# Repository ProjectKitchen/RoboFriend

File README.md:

# Robofriend

Robofriend - a semi-autonomous, remotely controllable robot companion.

Robofriend - initially created by Tom Heike 2002 - was exhibited at several Roboexotica events, serving drinks at the Vienniese Cocktail Robot Festival.
In 2014, two Robofriends were donated by Tom to us, and were further developed by Dr. Wummi and Karima Khlousy-Neirukh and other students at UAS Technikum Wien, in order to make Robofriend a playful companion robot which can be evaluated together with kids with special needs in selected schools in Vienna.
For this purpose, several game applications were developed which involve robot movements and expressions.

## Features
* live video transmission (low latency, < 300ms)
* remote control via webbrowser or game apps
* proximity sensors for collision avoidance & activity detection
* facial expressions, sound/voice playback, illuminated ears
* RFID reader - utilized for game interaction
* unique design (with CRT-head) by Tom Heike

## System Architecture / Components

The Robofriend uses a Teensy++ 2.0 microcontroller to handle motor control, led lights, servos, proximity sensors and battery status...
The Teensy is connected to the RaspberryPi via USB (/dev/ttyACM0). The RaspberryPi communicates with the Teensy via a simple protocol (ASCII-commands).
The RaspberryPi handles most of the robot's functions such as: RFID reader, CRT monitor, video camera, LED ears, speech output, ...

## User Interface and Control Options

The RaspberryPi starts a webserver which provides a webpage with live video feed and control interface.
It can be reached via http://<ip-adress-of-raspberry>:8765

The webpage uses an API to control the robots functions - this API is described in the theses of Karima Khlousy Neirukh (folder /documentation).
Furthermore, dedicated games have been developed by Karima which utilize the RFID-reader so that kids can use physical objects to interact with the robo and play litte games (identify animal sounds, emotions etc.)
These game applications are also written in python and are usually launched on a seperated tablet computer. The tablet connect to the python main script via a UDP connection (port 9000) and uses the same commands as the web GUI. It is planned to use a REST API for both (webpage and tablet GUI).

## Requirements

**Mjpg-Streamer:**
*  [MJPEG-Streamer Install & Setup](https://github.com/cncjs/cncjs/wiki/Setup-Guide:-Raspberry-Pi-%7C-MJPEG-Streamer-Install-&-Setup-&-FFMpeg-Recording)

**OpenCV 3:**
* To install OpenCV 3 on a Raspberry Pi 3 follow the following tutorial (except the virtual environment part):
[OpenCV 3 on Raspberry Pi 3](https://www.pyimagesearch.com/2017/09/04/raspbian-stretch-install-opencv-3-python-on-your-raspberry-pi/)

**Roboter Operating System (ROS):**
* To install ROS on your computing unit (Laptop or Rasberry Pi 3) follow [these instructions](https://github.com/ProjectKitchen/RoboFriend/tree/ros-node-devel/src/Pi/scripts)

**LIDAR - 360 laser distance sensor lds-01:**
* Manufacturer's [site](http://www.robotis.us/360-laser-distance-sensor-lds-01-lidar/)
* Set permission for the LDS-01 sensor after connecting it to the USB interface:
   * sudo chmod a+rw /dev/ttyUSBx

## Additional Information

* We recommand you to clone the repository into a folder named *Git* placed in your home directory (~/Git/)
* After pulling the repository, execute following commands (see the ROS install instructions):
   * cd ~/Git/RoboFriend/src/Pi/catkin_ws/ && rm -r build/ && rm -r devel/ && catkin_make clean && catkin_make && catkin_make
* To start face detection and object detection on external laptop enter *./start_computervision.sh "IP_ADDRESS_OF_RASPBERRY_PI"*

## Setup

Setup scripts are provided in folder /src/Pi/scripts

## Startup

Startup scripts are provided in folder /src/Pi/

## Future Plans

As next steps, several high-levels skills for Robofriend are planned:
* indoor localisation using ROS navigation stack (in order to find charging station)
* speech interaction (mic-array, beamforming, DOA, hotword detection)
* image analysis of live camera feed (face detection, facial landmark classification)

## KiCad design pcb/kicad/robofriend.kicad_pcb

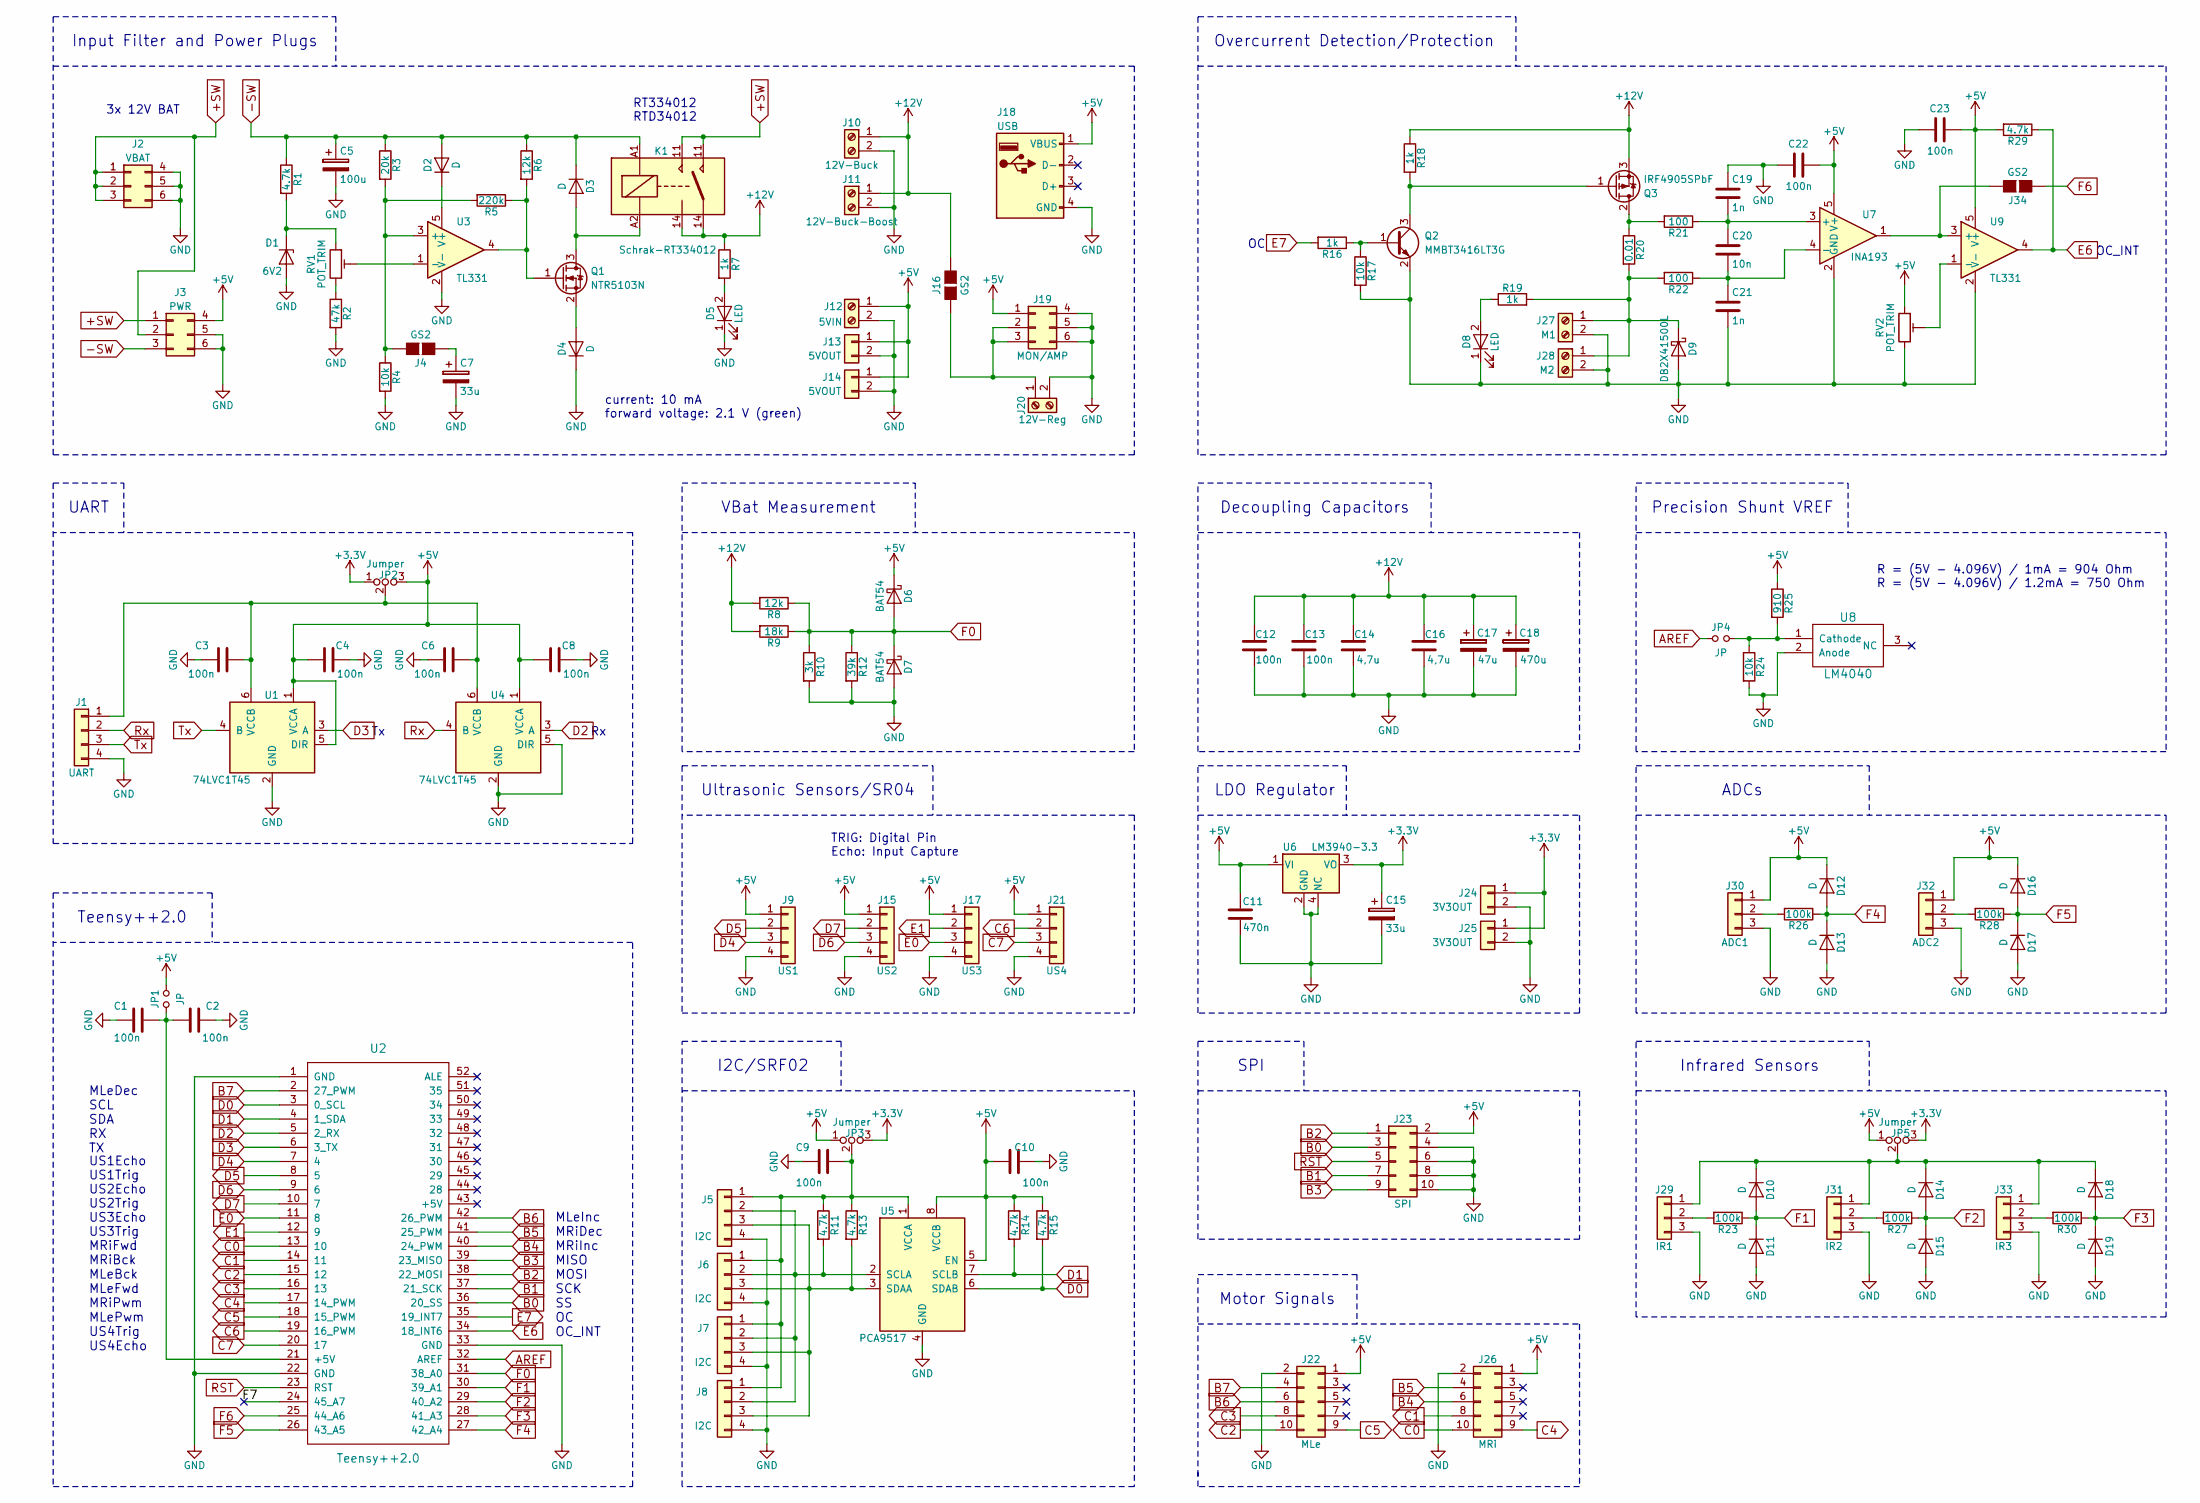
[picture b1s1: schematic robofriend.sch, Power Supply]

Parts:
C1, C2, C3, C4, C6, C8, C9, C10: 100n; C_0603
C5: 100u; CP_Elec_6.3x5.7; Part No EEE1CA101WAP
C7: 33u; CP_Elec_5x5.7; Part No EEE1CA330WR
C11: 470n; C_0805
C12, C13, C22, C23: 100n; C_0805
C14, C16: 4,7u; C_0805
C15: 33u; CP_Elec_4x5.7; Part No EEE0JA330WR
C17: 47u; CP_Elec_6.3x5.8; Part No EEEFK1C470P
C18: 470u; CP_Elec_8x10.5; Part No EEEFK1C471P
C19, C21: 1n; C_0805
C20: 10n; C_0805
D1: 6V2; D_SOD-123
D2, D4: D; D_SOD-323
D3: D; D_SOD-123
D5, D8: LED; LED_0805
D6, D7: BAT54; D_SOD-323; Part No BAT54WS-7-F
D9: DB2X41500L; D_SOD-123; Part No DB2X41500L
D10, D11, D12, D13, D14, D15, D16, D17, D18, D19: D; D_SOD-523
J1: UART; Pin_Header_Straight_1x04_Pitch2.54mm
J2: VBAT; Molex_MiniFit-JR-5556-06A_2x03x4.20mm_Straight
J3: PWR; Molex_MiniFit-JR-5556-06A_2x03x4.20mm_Straight
J4, J16, J34: GS2
J5, J6, J7, J8: I2C; Pin_Header_Straight_1x04_Pitch2.54mm
J9: US1; Pin_Header_Straight_1x04_Pitch2.54mm
J10: 12V-Buck; Molex_MiniFit-JR-5556-02B_2x01x4.20mm_Straight
J11: 12V-Buck-Boost; Molex_MiniFit-JR-5556-02B_2x01x4.20mm_Straight
J12: 5VIN; Molex_MiniFit-JR-5556-02B_2x01x4.20mm_Straight
J13, J14: 5VOUT; Pin_Header_Straight_2x01_Pitch2.54mm
J15: US2; Pin_Header_Straight_1x04_Pitch2.54mm
J17: US3; Pin_Header_Straight_1x04_Pitch2.54mm
J18: USB; WURTH_61400416021; Part No 48258-0001
J19: MON/AMP; Molex_MiniFit-JR-5556-06A_2x03x4.20mm_Straight
J20: 12V-Reg; Molex_MiniFit-JR-5556-02B_2x01x4.20mm_Straight
J21: US4; Pin_Header_Straight_1x04_Pitch2.54mm
J22: MLe; Pin_Header_Straight_2x05_Pitch2.54mm
J23: SPI; Pin_Header_Straight_2x05_Pitch2.54mm
J24, J25: 3V3OUT; Pin_Header_Straight_2x01_Pitch2.54mm
J26: MRi; Pin_Header_Straight_2x05_Pitch2.54mm
J27: M1; Molex_MiniFit-JR-5556-02B_2x01x4.20mm_Straight
J28: M2; Molex_MiniFit-JR-5556-02B_2x01x4.20mm_Straight
J29: IR1; Pin_Header_Straight_1x03_Pitch2.54mm
J30: ADC1; Pin_Header_Straight_1x03_Pitch2.54mm
J31: IR2; Pin_Header_Straight_1x03_Pitch2.54mm
J32: ADC2; Pin_Header_Straight_1x03_Pitch2.54mm
J33: IR3; Pin_Header_Straight_1x03_Pitch2.54mm
JP1, JP4: JP; Pin_Header_Straight_1x02_Pitch2.54mm
JP2, JP3, JP5: Jumper; Pin_Header_Straight_1x03_Pitch2.54mm
K1: Schrak-RT334012; SPST_Schrack-RT33_RM5mm
Q1: NTR5103N; SOT-23
Q2: MMBT3416LT3G; SOT-23
Q3: IRF4905SPbF; TO-263-2
R1, R29: 4.7k; R_0805
R2: 47k; R_0805
R3: 20k; R_0805
R4, R17: 10k; R_0805
R5: 220k; R_0805
R6, R8: 12k; R_0805
R7, R16, R18, R19: 1k; R_0805
R9: 18k; R_0805
R10: 3k; R_0805
R11, R13, R14, R15: 4.7k; R_0603
R12: 39k; R_0805
R20: 0.01; R_2512; Part No WSL2512R0100FEK
R21, R22: 100; R_0805
R23, R26, R27, R28, R30: 100k; R_0603
R24: 10k; R_0603
R25: 910; R_0603
RV1, RV2: POT_TRIM; Potentiometer_Trimmer_Bourns_3296W; Part No 3296W-1-104LF
U1, U4: 74LVC1T45; SOT-363_SC-70-6
U2: Teensy++2.0; Teensy2.0++
U3, U9: TL331; SOT-23-5
U5: PCA9517; SOIC-8_3.9x4.9mm_Pitch1.27mm
U6: LM3940-3.3; SOT-223
U7: INA193; SOT-23-5
U8: LM4040; SOT-23

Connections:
+3V3: C15.1, J24.1, J25.1, JP2.1, JP3.3, JP5.3, U6.3 (VO)
+5V: C4.1, C8.1, C10.1, C11.2, C22.2, C23.2, D6.1 (K), D12.1 (K), D16.1 (K), J3.4, J9.1, J12.1, J13.1, J14.1, J15.1, J17.1, J18.1 (VBUS), J19.1, J21.1, J22.1, J23.2, J26.1, J30.1, J32.1, JP1.2, JP2.3, JP3.1, JP5.1, R14.1, R15.1, R25.1, R29.2, RV2.1, U1.1 (VCCA), U1.5 (DIR), U4.1 (VCCA), U5.5 (EN), U5.8 (VCCB), U6.1 (VI), U7.5 (V+), U9.5 (V+)
+12V: C12.2, C13.2, C14.2, C16.2, C17.1, C18.1, J10.1, J11.1, J16.2 (G2), K1.14, Q3.3 (S), R7.1, R8.2, R9.2, R18.1
+SW: J2.1, J2.2, J2.3, J3.1, J3.2, K1.11
-SW: C5.1, D2.2 (A), D3.1 (K), J3.3, K1.A1, R1.1, R3.1, R6.1
AREF: JP4.1, U2.32 (AREF)
B0: J23.3, U2.36 (20_SS)
B1: J23.7, U2.37 (21_SCK)
B2: J23.1, U2.38 (22_MOSI)
B3: J23.9, U2.39 (23_MISO)
B4: J26.6, U2.40 (24_PWM)
B5: J26.4, U2.41 (25_PWM)
B6: J22.6, U2.42 (26_PWM)
B7: J22.4, U2.2 (27_PWM)
C0: J26.10, U2.13 (10)
C1: J26.8, U2.14 (11)
C2: J22.10, U2.15 (12)
C3: J22.8, U2.16 (13)
C4: J26.9, U2.17 (14_PWM)
C5: J22.9, U2.18 (15_PWM)
C6: J21.2, U2.19 (16_PWM)
C7: J21.3, U2.20 (17)
D0: R15.2, U2.3 (0_SCL), U5.6 (SDAB)
D1: R14.2, U2.4 (1_SDA), U5.7 (SCLB)
D2: U2.5 (2_RX), U4.3 (A)
D3: U1.3 (A), U2.6 (3_TX)
D4: J9.3, U2.7 (4)
D5: J9.2, U2.8 (5)
D6: J15.3, U2.9 (6)
D7: J15.2, U2.10 (7)
E0: J17.3, U2.11 (8)
E1: J17.2, U2.12 (9)
E6: R29.1, U2.34 (18_INT6), U9.4
E7: R16.2, U2.35 (19_INT7)
F0: D6.2 (A), D7.1 (K), R8.1, R9.1, R10.1, R12.1, U2.31 (38_A0)
F1: D10.2 (A), D11.1 (K), R23.1, U2.30 (39_A1)
F2: D14.2 (A), D15.1 (K), R27.1, U2.29 (40_A2)
F3: D18.2 (A), D19.1 (K), R30.1, U2.28 (41_A3)
F4: D12.2 (A), D13.1 (K), R26.1, U2.27 (42_A4)
F5: D16.2 (A), D17.1 (K), R28.1, U2.26 (43_A5)
F6: J34.1 (G1), U2.25 (44_A6)
GND: C1.2, C2.1, C3.2, C4.2, C5.2, C6.2, C7.2, C8.2, C9.2, C10.2, C11.1, C12.1, C13.1, C14.1, C15.2, C16.1, C17.2, C18.2, C19.1, C21.2, C22.1, C23.1, D1.2 (A), D4.1 (K), D5.1 (K), D7.2 (A), D8.1 (K), D9.2 (A), D11.2 (A), D13.2 (A), D15.2 (A), D17.2 (A), D19.2 (A), J1.4, J2.4, J2.5, J2.6, J3.5, J3.6, J5.4, J6.4, J7.4, J8.4, J9.4, J10.2, J11.2, J12.2, J13.2, J14.2, J15.4, J17.4, J18.4 (GND), J19.4, J19.5, J19.6, J20.2, J21.4, J22.2, J23.4, J23.6, J23.8, J23.10, J24.2, J25.2, J26.2, J27.2, J28.2, J29.3, J30.3, J31.3, J32.3, J33.3, Q2.2 (E), R2.2, R4.2, R10.2, R12.2, R17.2, R24.2, RV2.3, U1.2 (GND), U2.1 (GND), U2.22 (GND), U2.33 (GND), U3.2 (V-), U4.2 (GND), U4.5 (DIR), U5.4 (GND), U6.2 (GND), U6.4 (NC), U7.2 (GND), U8.2 (Anode), U9.2 (V-)
unnamed: C1.1, C2.2, JP1.1, U2.21 (+5V)
unnamed: C3.1, C6.1, J1.1, JP2.2, U1.6 (VCCB), U4.6 (VCCB)
unnamed: C7.1, J4.1 (G1)
unnamed: C9.1, J5.1, J6.1, J7.1, J8.1, JP3.2, R11.1, R13.1, U5.1 (VCCA)
unnamed: C19.2, C20.1, R21.1, U7.3 (+)
unnamed: C20.2, C21.1, R22.1, U7.4 (-)
unnamed: D1.1 (K), R1.2, RV1.1
unnamed: D2.1 (K), U3.5 (V+)
unnamed: D3.2 (A), K1.A2, Q1.3 (D)
unnamed: D4.2 (A), Q1.2 (S)
unnamed: D5.2 (A), R7.2
unnamed: D8.2 (A), R19.1
unnamed: D9.1 (K), J27.1, J28.1, R19.2, R20.2, R22.2
unnamed: D10.1 (K), D14.1 (K), D18.1 (K), J29.1, J31.1, J33.1, JP5.2
unnamed: J4.2 (G2), R3.2, R4.1, R5.2, U3.3 (+)
unnamed: J5.2, J6.2, J7.2, J8.2, R11.2, U5.2 (SCLA)
unnamed: J5.3, J6.3, J7.3, J8.3, R13.2, U5.3 (SDAA)
unnamed: J16.1 (G1), J19.2, J19.3, J20.1
unnamed: J29.2, R23.2
unnamed: J30.2, R26.2
unnamed: J31.2, R27.2
unnamed: J32.2, R28.2
unnamed: J33.2, R30.2
unnamed: J34.2 (G2), U7.1, U9.3 (+)
unnamed: JP4.2, R24.1, R25.2, U8.1 (Cathode)
unnamed: Q1.1 (G), R5.1, R6.2, U3.4
unnamed: Q2.1 (B), R16.1, R17.1
unnamed: Q2.3 (C), Q3.1 (G), R18.2
unnamed: Q3.2 (D), R20.1, R21.2
unnamed: R2.1, RV1.3
unnamed: RV1.2, U3.1 (-)
unnamed: RV2.2, U9.1 (-)
RST: J23.5, U2.23 (RST)
Rx: J1.2, U4.4 (B)
Tx: J1.3, U1.4 (B)

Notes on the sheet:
current: 10 mA forward voltage: 2.1 V (green)
R = (5V - 4.096V) / 1mA = 904 Ohm R = (5V - 4.096V) / 1.2mA = 750 Ohm
RT334012 RTD34012
TRIG: Digital Pin Echo: Input Capture
MLeDec SCL SDA RX TX
MRiFwd MRiBck MLeBck MLeFwd MRiPwm MLePwm US4Trig US4Echo
Infrared Sensors
ADCs
Overcurrent Detection/Protection
SPI
Ultrasonic Sensors/SR04
Motor Signals
UART
I2C/SRF02
Precision Shunt VREF
Teensy++2.0
MLeInc MRiDec MRiInc MISO MOSI SCK SS OC OC_INT
US1Echo US1Trig US2Echo US2Trig US3Echo US3Trig
VBat Measurement
Decoupling Capacitors
LDO Regulator
Input Filter and Power Plugs
OC_INT
3x 12V BAT

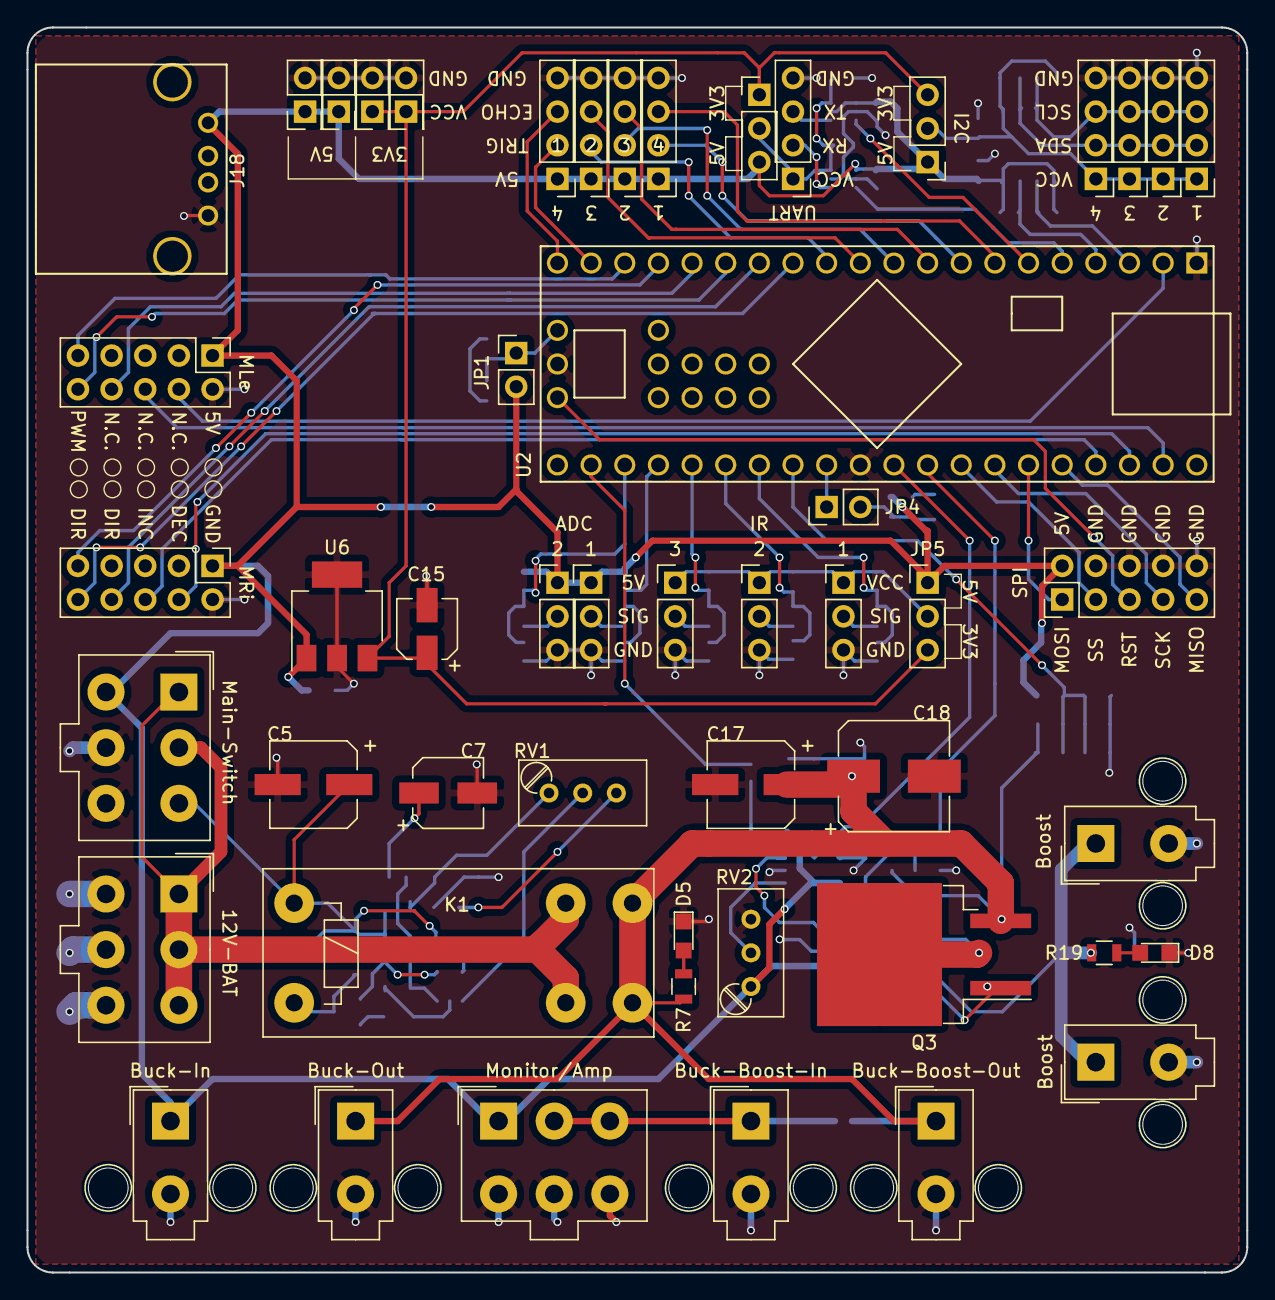
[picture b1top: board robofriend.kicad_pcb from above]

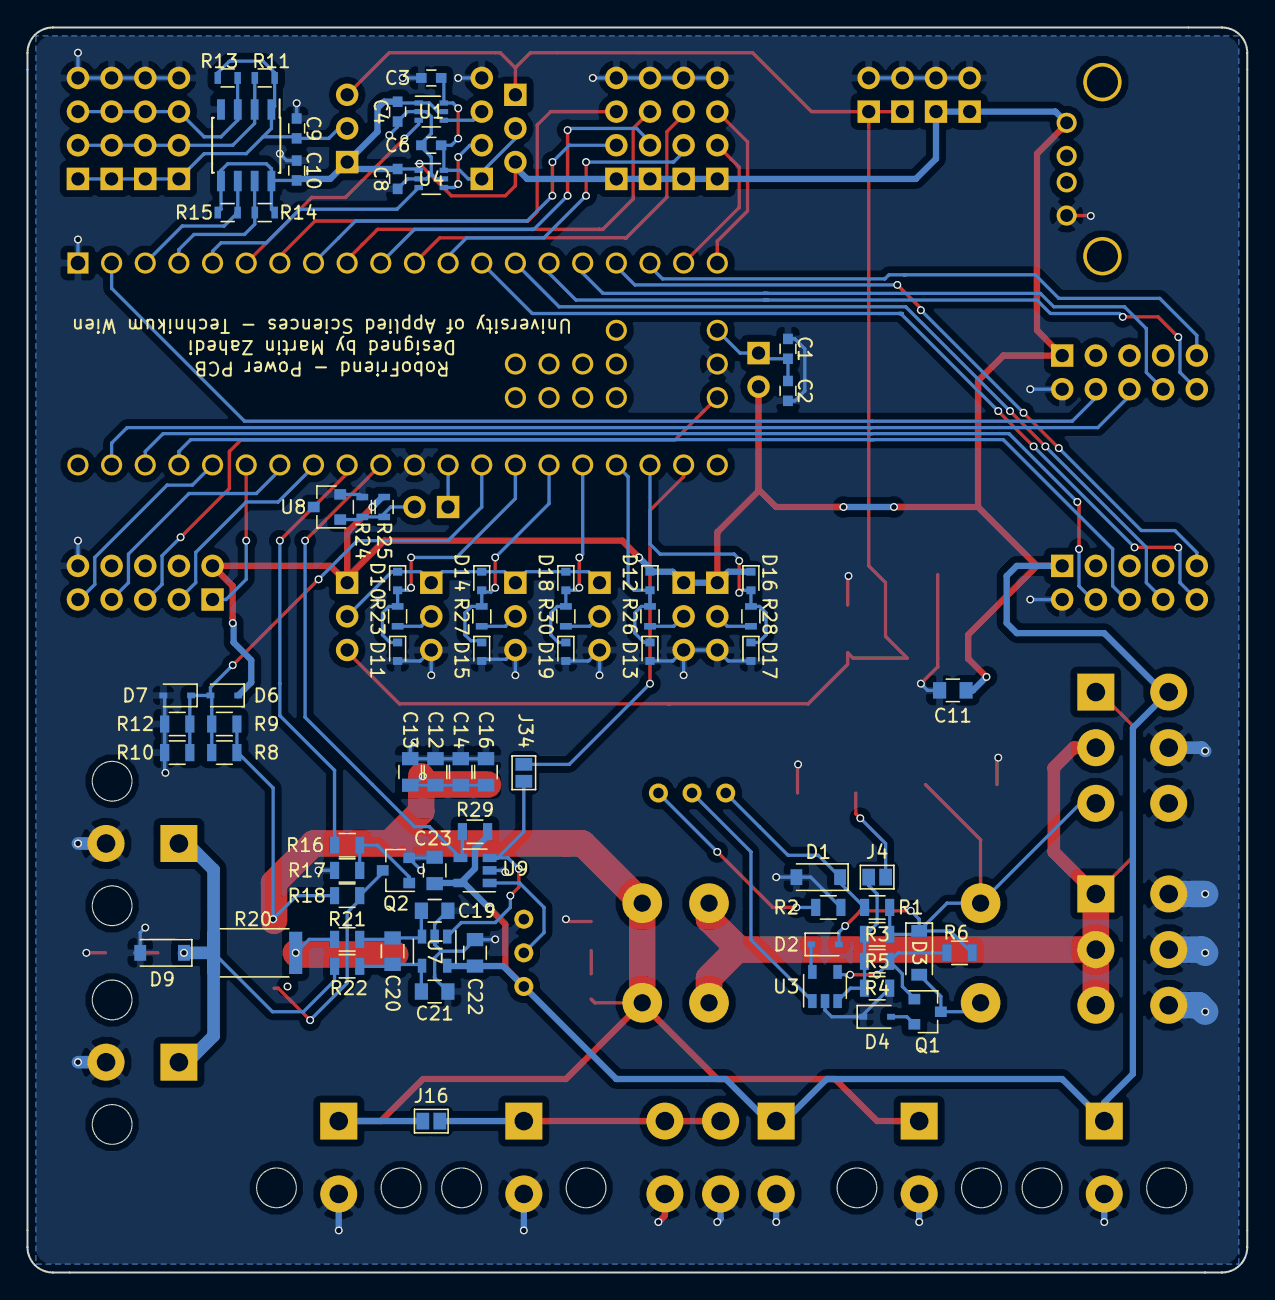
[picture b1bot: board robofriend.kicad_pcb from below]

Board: 2 copper layers, 92.1 x 94.0 mm, 126 parts (75 on the bottom side), 77 nets.

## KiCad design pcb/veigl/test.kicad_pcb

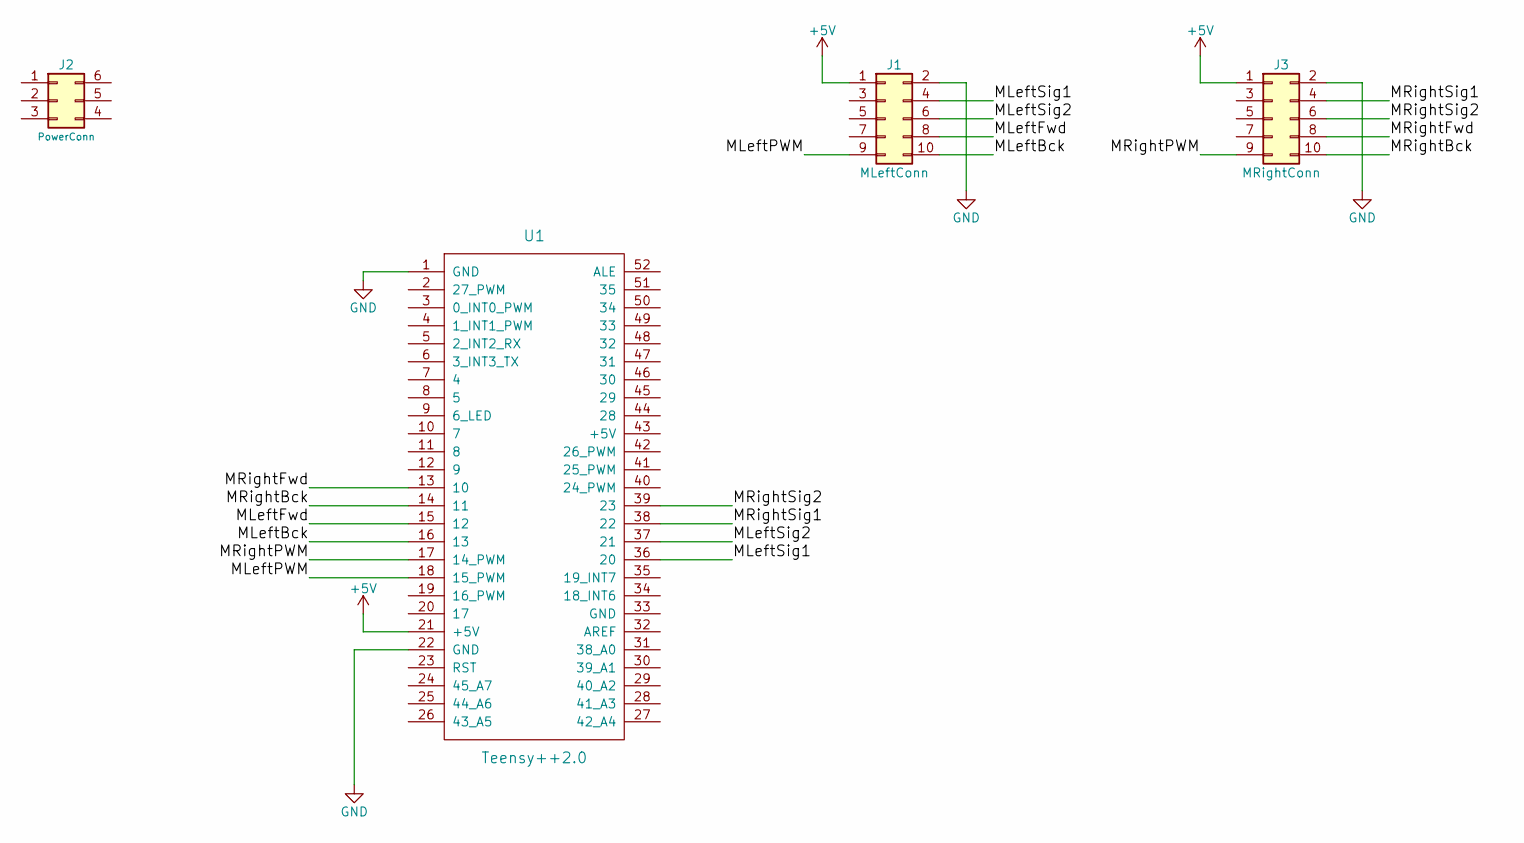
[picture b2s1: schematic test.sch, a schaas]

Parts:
J1: MLeftConn; Pin_Header_Straight_2x05_Pitch2.54mm
J2: PowerConn; Molex_MiniFit-JR-5556-06B_2x03x4.20mm_Straight
J3: MRightConn; Pin_Header_Straight_2x05_Pitch2.54mm
U1: Teensy++2.0; Teensy2.0++

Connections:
+5V: J1.1, J3.1, U1.21 (+5V)
/MLeftBck: J1.10, U1.16 (13)
/MLeftFwd: J1.8, U1.15 (12)
/MLeftPWM: J1.9, U1.18 (15_PWM)
/MLeftSig1: J1.4, U1.36 (20)
/MLeftSig2: J1.6, U1.37 (21)
/MRightBck: J3.10, U1.14 (11)
/MRightFwd: J3.8, U1.13 (10)
/MRightPWM: J3.9, U1.17 (14_PWM)
/MRightSig1: J3.4, U1.38 (22)
/MRightSig2: J3.6, U1.39 (23)
GND: J1.2, J3.2, U1.1 (GND), U1.22 (GND)

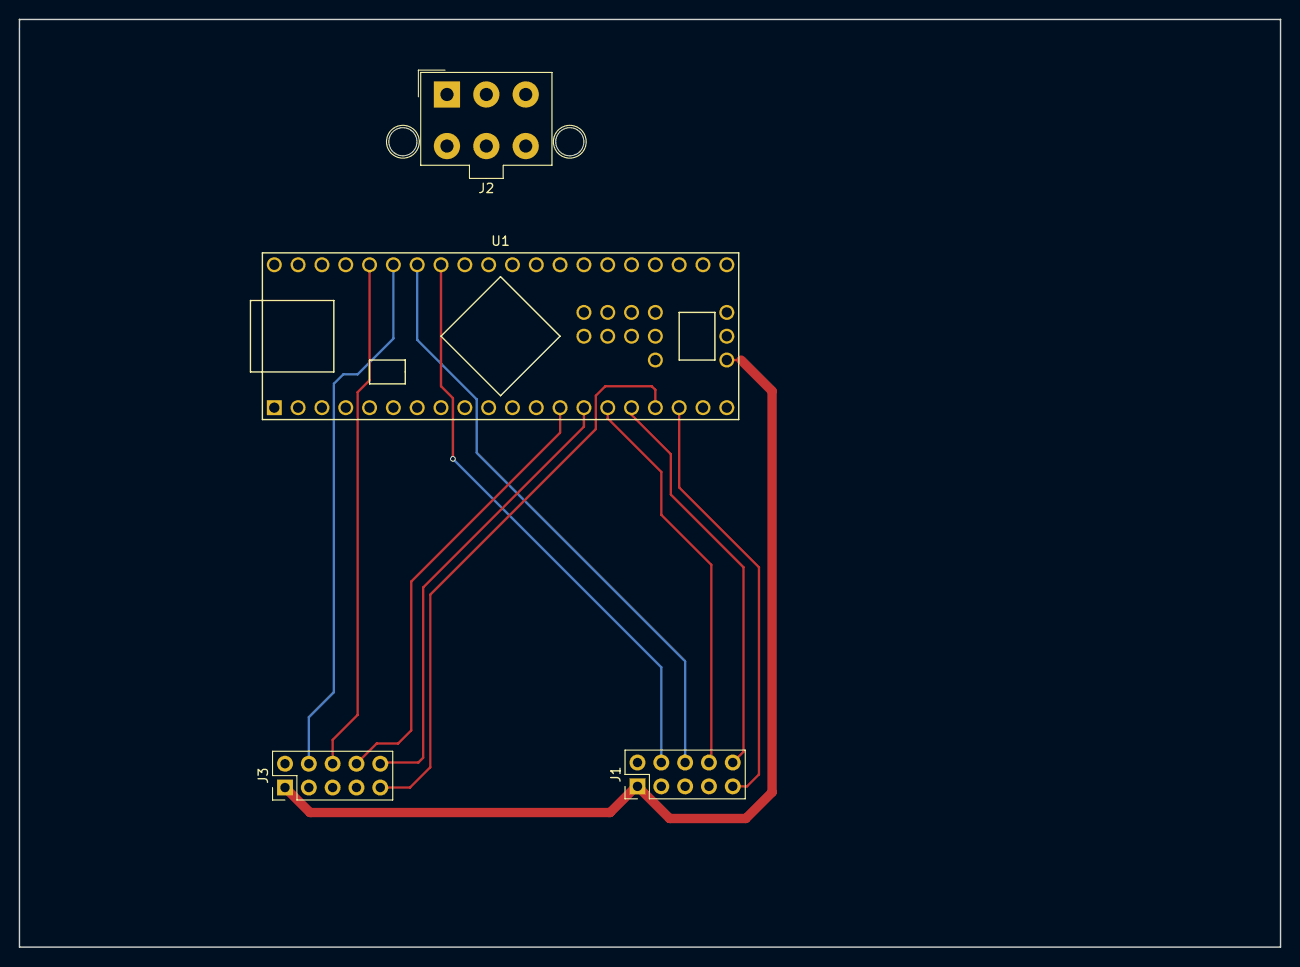
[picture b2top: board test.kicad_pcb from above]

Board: 2 copper layers, 134.5 x 98.9 mm, 4 parts (0 on the bottom side), 12 nets.

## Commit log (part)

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2019-01-16 Minior changes
2019-01-23 Bug fixing
2019-01-23 minor changes
2019-01-23 starting to merge
2019-01-23 starting to make robofriend run again :)
2019-01-26 adding rplidar driver to ros project
2019-01-26 get robobrainFacedetection into running condition / not running yet
2019-01-26 adding the lds driver as a submodule
2019-01-26 changing submodule
2019-01-26 refering to the melodic-devel branch of the submodule
2019-01-26 adding turtlebot3 submodules
2019-01-26 finished with lidar driver - trying to adapt slam into project - still have a launch problem
2019-01-26 fixed launch problem
2019-01-27 add removed variables / bug fix
2019-01-27 start node
2019-01-27 changes in order to capture pictures via webcam / bug fix
2019-01-27 implement function to record new faces
2019-01-27 start with function to record 15 pictures
2019-01-27 function to record pictures implemented / not tested yet
2019-01-28 adding script files to the project, adapting documentation
2019-01-28 minor changes on start scripts
2019-01-28 added startrobo.desktop
2019-01-29 minor change on gitignore
2019-01-29 adapting scripts and documentation
2019-01-29 trying to run tb3 via remote pc
2019-01-30 Add new service to enable creation of new database
2019-01-30 implement logic to create new database
2019-01-30 change topic name
2019-01-30 Service to enable the creation of a new database
2019-01-30 minor beautification
2019-01-31 implement service response to check if face detection node has started when not started then always change to idle state
2019-01-31 start of replacing print log messages by ros log messages
2019-02-01 implement logic to ask before taking a new pciture and check if the entered name already exists/ not tested yet
2019-02-01 modify in order to check if name already exists
2019-02-02 Minior changes and clean up
2019-02-02 logic to ask known person for further recordings is implemented
2019-02-02 modify prints
2019-02-17 create class and add service handler to activate a specific hotword
2019-02-17 logic to conect and to seperate slots added / not finished yet
2019-02-17 function to start voice detection node added
2019-02-18 create Hotword Detection Service
2019-02-18 implement function to handle an incoming hot word detection request
2019-02-18 start to implement brain node logic regarding voice detection
2019-02-22 cleaning up simulation folder
2019-02-22 adding simulation for vbat meas
2019-02-22 minor changes on schematics
2019-02-25 bug fixes and other things
2019-02-25 Beatufication
2019-02-25 start implementing
2019-02-26 get voice detection operational
2019-02-26 audio interaction operational
2019-02-26 established rviz incl. laser scan and map for tb usage
2019-03-04 start implementing computer vision
2019-03-07 some changes and deletions on the teensy logic
2019-03-07 changing some var names
2019-03-07 reviewed sensors module
2019-03-07 finished major clean up and adaptations .. added soft and hard stop for the motors ..
2019-03-07 added watchdog (8s)
2019-03-08 added over current proteciton logic (digital)
2019-03-08 adding detachInterrupt routines to destructors
2019-03-08 minor clean up
2019-03-08 making launch files runable again
2019-03-09 further clean up
2019-03-09 implement logic to handle incoming messages
2019-03-09 get script operational / big fixing
2019-03-09 removed old constants module
2019-03-09 minor change on start script
2019-03-09 added system termination method to systemModule
2019-03-09 further adaption on rfid module
2019-03-09 code rewritten / shutdown logic and ros launch has to be imlemented
2019-03-09 thread removed
2019-03-10 code adaptation for all sensor data (zahedim)
2019-03-10 moved systemModule
2019-03-10 moved serial handlers
2019-03-10 still having some threading problems
2019-03-10 adapting launch files
2019-03-10 adapting start script
2019-03-10 added game communicator to ros
2019-03-11 we have now are udp socket - but the logic is not working correctly - shouldnt affect other nodes
2019-03-11 working state with dump data decision
2019-03-11 teensyCommunicator now able to send different commands to teensy
2019-03-11 stablished communication between game- and teensycommunicator
2019-03-11 merging battery state and infrared msgs to state module data for better handling
2019-03-11 simplified stopMovement logic
2019-03-13 adapted status module nearly to the end
2019-03-13 udp socket sending bat volt information to app per status;info request
2019-03-14 providing webserver with pcb sensor data and saving map via webserver done
2019-03-14 removed some todos
2019-03-15 starting ros nodes through launch file
2019-03-15 module rewritten in order to start node through launch file
2019-03-15 speech node to start in launch file added
2019-03-15 print by ros-print functions removed
2019-03-15 module rewritten in order to start node with launch file
2019-03-15 data handler merged into one file
2019-03-16 Servo Cam Node added to launch Node through launch file
2019-03-16 Mnior changes
2019-03-16 Data handler is added into main file
2019-03-16 Led Ears Node added to start Node trough launch file
2019-03-16 data hander is added into main file
2019-03-16 Service for handling the position of the servo camera added
2019-03-16 service to handle the camera position from the webserver added
2019-03-16 logic to hanlde incoming messages from the service implemented
2019-03-16 Constants regarding camera position added
2019-03-16 Service to handle the leds added
2019-03-16 service and constants for led configuration added
2019-03-16 logic to handle incoming requests from webserver added
2019-03-16 added a solder jumper to connect the buck-boost-out and buck-boost-in
2019-03-16 minor changes on layout
2019-03-17 add speech service
2019-03-17 files merged into one file
2019-03-17 constants regarding speech node functions added
2019-03-17 services and service response handler implemented
2019-03-17 service to handle speech actions implemented / not finished yet
2019-03-17 Minior chnages
2019-03-17 interaction between webserver and speech node finished
2019-03-17 beautification on webserver
2019-03-18 to start node through launch file
2019-03-18 Data Handlers merged into main files
2019-03-18 rewritting faceModule to to ROS Node / functions implemented and first testings accomplished
2019-03-18 Services to communicate with face node implemented
2019-03-18 starting to implement logic to get Screenshot
2019-03-19 testing teensy pi interface
2019-03-19 removed test blocks
2019-03-19 service to handle timestamp added
2019-03-19 service to trigger timestamp added
2019-03-21 adapted launch file
2019-03-21 battery measurement successful
2019-03-21 logic to adjust the eyes implemented
2019-03-21 only ready sensor data from teensy to prevent errors in log
2019-03-21 Todos removed
2019-03-22 multithreading for game communicator - not finished yet
2019-03-22 implemented threads into the game communicator module
2019-03-25 reading the shunt amp voltage and sending it to pi
2019-03-26 new services to communicate with webserver/face node implemented
2019-03-26 to start sound node through launch file added
2019-03-26 logic to enable playing sound during the game is added
2019-03-26 logic to playing sounds through webserver added
2019-03-26 new services added
2019-03-26 rewritting of existing sound Module in order to start through launch file
2019-03-26 sound files moved
2019-03-26 changes due to service message changes
2019-03-26 files added to start from launch file
2019-03-28 Bring up modifications
2019-03-28 solving IOWarrior Issue
2019-03-31 start with implementing of object detection
2019-03-31 logic to detetect Object and to trigger start through service implemented
2019-03-31 node modified in order to handle situation when mjpg streamer is not started
2019-03-31 launch file created to start nodes from extrenal laptop
2019-04-06 start of face-detection Node removed since node is started through other launch file
2019-04-06 IP address of the Pi added
2019-04-07 restoring previous functionalities within ros enviroment / teensy commands finished
2019-04-07 since publishers are implemented in data handlers not needed any more
2019-04-07 face manipulation logic through keyboard added
2019-04-07 response function added
2019-04-07 garbage file
2019-04-07 additional information added
2019-04-08 logic to enter desired ADV interaction mode added
2019-04-08 start implementing behavioural interactions
2019-04-08 modifications in order to enable behavioural interaction
2019-04-08 Due to modifications in RobobrainFaceDetectionHandler minior changes in Status Handler
2019-04-09 parts which are dealing with voice detecting and smart home interaction are removed
2019-04-09 implementing the randomly selection of voice interaction
2019-04-09 Majour changes
2019-04-10 terminating issue solved
2019-04-10 Code improvement
2019-04-10 add logic to start object/person detection
2019-04-10 add text in order to speak in idle mode
2019-04-10 implement logic to start pbject detection
2019-04-10 changing logwarn into logdebug
2019-04-10 voice interactiion possibilietis regarding familliarity of person added / not fiished yet
2019-04-10 voice detection packages added
2019-04-11 Possible solution for speech issue
2019-04-12 adapted u10, pull-up on schematic
2019-04-12 removed u6, impedance converter from schematic
2019-04-13 changes due to sound issue
2019-04-13 changes in order to enable setting the IP address of the mjpg streamer trough start_computervision.sh
2019-04-13 same problem like speech module / problem solved
2019-04-13 scrpt to set the ip address of facedetection node and objectdetetcion node
2019-04-13 Heartbeat service for facedetection added
2019-04-13 service to reply HB request added
2019-04-13 Logic to enable HB Services implemented
2019-04-14 Heartbeat message to check status of Object detection node implemented
2019-04-14 logic to send an receive heartbeat services added
2019-04-14 callback to catch pressed buttons regarding AVI States implemented
2019-04-14 Define Message to publish to RobobrainStateHandler
2019-04-14 logic to change avi state with a phrase implemented
2019-04-14 Subscriber to receive messages from webserver added / logic to handle entered phrases from webserver added
2019-04-15 adapted motor pins on schematic
2019-04-15 major changes on schematic
2019-04-15 hardware bugs fixed in schematic
2019-04-16 adapted lower thrashold for deep discharge circuit
2019-04-16 adapted pcb layout for hw rev ii
2019-04-16 generated gerber, drill files and plot
2019-04-17 Add lock and a delay in Speech Node
2019-04-17 change speak time to increase the intervals
2019-04-18 Add second value
2019-04-21 logic to control other smart home devices added
2019-04-21 logic to control smart home devices added
2019-04-21 logwarn replaced by logdebug
2019-04-21 speech in case of no detected person implemented
2019-04-21 model modification
2019-04-22 finishing docu
2019-04-22 add publisher to communicate with led node and to set camera position
2019-04-22 add logic to set led color
2019-04-22 adding further docu
2019-04-22 since computervison noder are started via bash script not needed anymore
2019-04-22 Minior changes and maybe last push of momokarl :)
2019-04-22 removed old python code, adapting launchfiles, beautifications
2019-04-22 furhter clean up
2019-04-22 final works on index.html file, zahedim's last commit :)
2019-04-22 commands to setup and install respeaker on pi
2019-04-22 file to install snips manually without sam created
2019-04-22 clean up
2019-04-22 Modify Readme and last push of momokarl :)
2019-04-30 fixed special literals
2019-04-30 removed superfluous single quote
2019-05-02 check if the expected amount of slots are detected
2019-05-02 publish message when expected amount of slots are not given
2019-05-14 added docu
2019-11-06 create new branch with new SW-Architecture
2020-01-02 update all sources robofriend can drive in charging station (without charging voltage)
2020-01-08 add code documentation
2020-01-31 add complet map of labor solve problem with teensy crashes add rosnode for snips/udp location goals
2024-05-08 changes for RP4 and X threading
2024-05-08 added composite/hdmi scripts, adapted proximity sensor thresholds
